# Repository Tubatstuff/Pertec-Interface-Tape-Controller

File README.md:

This is the repository for a controller to formatted Pertec tape interface.

The directories are as follows:

	doc - Documentation
	firmware - Controller firmware
	kicad - KiCAD schematics, board layout, etc.

The firmware can be built from source using the gcc-arm-none-eabi compiler
and the libopencm3 development library (libopencm3.org) which is covered by
the GNU General Public License v3.0, as is this project.

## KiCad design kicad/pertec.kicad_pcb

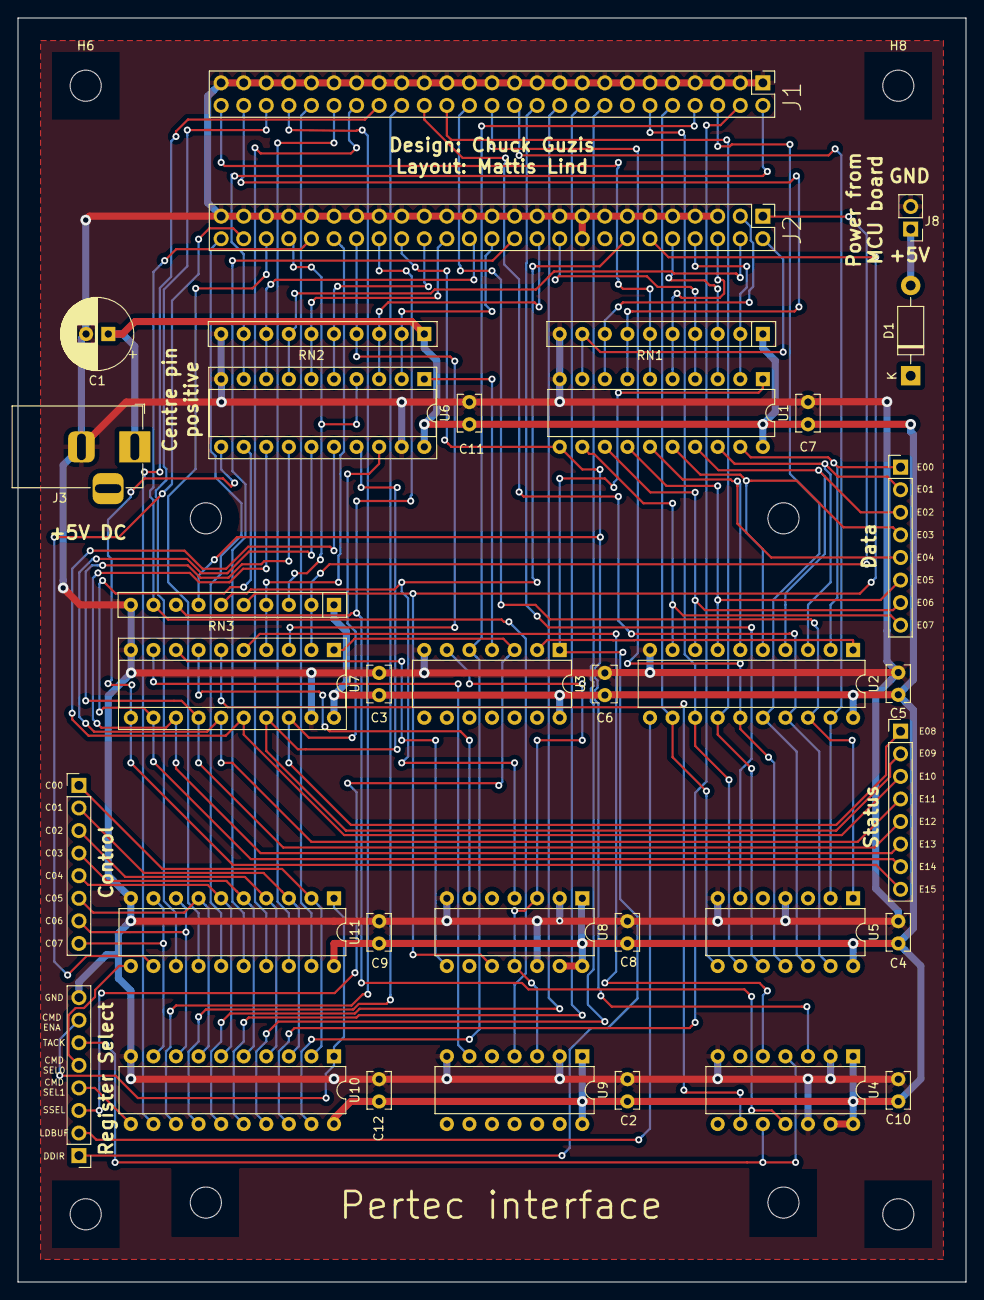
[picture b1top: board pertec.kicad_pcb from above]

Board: 2 copper layers, 106.7 x 142.2 mm, 43 parts (0 on the bottom side), 91 nets.

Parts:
C1: 470/16; CP_Radial_D8.0mm_P2.50mm
C2, C3, C4, C5, C6, C7, C8, C9, C10, C11, C12: 104; C_Rect_L4.0mm_W2.5mm_P2.50mm
D1: 1N5817; D_DO-41_SOD81_P10.16mm_Horizontal
H1, H2, H3, H4, H5, H6, H7, H8: MountingHole; MountingHole_3.5mm
J1, J2: Conn_02x25_Odd_Even; PinHeader_2x25_P2.54mm_Vertical
J3: +5 VDC; BarrelJack_Horizontal
J4: Data 0:7; PinHeader_1x08_P2.54mm_Vertical
J5: Status 0:7; PinHeader_1x08_P2.54mm_Vertical
J6: Control; PinHeader_1x08_P2.54mm_Vertical
J7: Register Select; PinHeader_1x08_P2.54mm_Vertical
J8: MCU Power; PinHeader_1x02_P2.54mm_Vertical
RN1, RN2, RN3: 220/330; R_Array_SIP10
U1, U2, U10, U11: 74LS574; DIP-20_W7.62mm
U3: 74LS04; DIP-14_W7.62mm
U4, U8, U9: 74LS74; DIP-14_W7.62mm
U5: 74LS280; DIP-14_W7.62mm
U6, U7: 74LS541; DIP-20_W7.62mm_Socket

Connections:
C00: J6.1, U10.2, U11.2
C01: J6.2, U10.3, U11.3
C02: J6.3, U10.4, U11.4
C03: J6.4, U10.5, U11.5
C04: J6.5, U10.6, U11.6
C05: J6.6, U10.7, U11.7
C06: J6.7, U10.8, U11.8
C07: J6.8, U10.9, U11.9
CMDENA: J7.7, U10.1, U11.1
CMDSEL0: J7.4, U10.11
CMDSEL1: J7.5, U11.11
DDIR: J7.1, U1.1, U3.1
E00: J4.1, U1.19, U2.2
E01: J4.2, U1.18, U2.3
E02: J4.3, U1.17, U2.4
E03: J4.4, U1.16, U2.5
E04: J4.5, U1.15, U2.6
E05: J4.6, U1.14, U2.7
E06: J4.7, U1.13, U2.8
E07: J4.8, U1.12, U2.9
E08: J5.1, U6.18, U7.18
E09: J5.2, U6.17, U7.17
E10: J5.3, U6.16, U7.16
E11: J5.4, U6.15, U7.15
E12: J5.5, U6.14, U7.14
E13: J5.6, U6.13, U7.13
E14: J5.7, U6.12, U7.12
E15: J5.8, U6.11, U7.11
GND: C1.2, C2.2, C3.2, C4.2, C5.2, C6.2, C7.2, C8.2, C9.2, C10.2, C11.2, C12.2, J1.1, J1.3, J1.5, J1.7, J1.9, J1.11, J1.13, J1.15, J1.17, J1.19, J1.21, J1.23, J1.25, J1.27, J1.29, J1.31, J1.33, J1.35, J1.37, J1.39, J1.41, J1.43, J1.45, J1.47, J1.49, J2.5, J2.7, J2.9, J2.11, J2.13, J2.15, J2.17, J2.18, J2.19, J2.21, J2.23, J2.25, J2.27, J2.29, J2.31, J2.33, J2.35, J2.37, J2.39, J2.41, J2.43, J2.45, J2.47, J2.49, J3.2, J7.8, J8.2, RN1.10, RN2.10, RN3.10, U1.10, U2.10, U3.7, U4.2, U4.7, U4.12, U5.4, U5.7, U6.10, U6.19, U7.10, U7.19, U8.2, U8.7, U8.12, U9.2, U9.7, U10.10, U11.10
ICER: J2.42, RN3.9, U9.4
IDBY: J2.38, RN2.4, U7.3
IEDIT: J1.38, U11.17
IEOT: J2.22, RN2.3, U6.3
IERASE: J1.40, U11.18
IFAD: J2.48, U11.12
IFBY: J1.2, RN2.9, U6.9
IFMK: J2.14, RN3.6, U8.4
IFPT: J2.32, RN2.5, U6.5
IGO: J1.8, U3.5, U10.19
IHER: J2.12, RN3.5, U8.10
IHSP: J2.50, U11.15
ILDP: J2.4, RN2.7, U6.7
ILOL: J1.16, U10.17
ILWD: J1.4, U10.18
IONL: J2.44, RN3.3, U6.4
IR0: J2.2, RN1.9, U1.9
IR1: J2.3, RN1.8, U1.8
IR2: J1.48, RN1.7, U1.7
IR3: J1.50, RN1.6, U1.6
IR4: J2.6, RN1.5, U1.5
IR5: J2.20, RN1.4, U1.4
IR6: J2.10, RN1.3, U1.3
IR7: J2.8, RN1.2, U1.2
IRDY: J2.28, RN2.8, U6.8
IREV: J1.18, U10.16
IREW: J1.20, U10.15
IRNZ: J2.26, RN2.2, U6.2
IRP: J2.1, RN3.2, U7.2
IRSTR: J2.34, RN3.7, U1.11, U4.3
IRTH1: J1.44, U10.13
IRTH2: J1.36, U10.12
IRWD: J2.30, RN2.6, U6.6
IRWU: J2.24, U11.16
ISPEED: J2.40, RN3.4, U7.4
ITAD0: J1.46, U11.13
ITAD1: J2.46, U11.14
IW0: J1.10, U2.12, U5.8
IW1: J1.12, U2.13, U5.9
IW2: J1.30, U2.14, U5.10
IW3: J1.26, U2.15, U5.11
IW4: J1.6, U2.16, U5.12
IW5: J1.32, U2.17, U5.13
IW6: J1.28, U2.18, U5.1
IW7: J1.24, U2.19, U5.2
IWFM: J1.42, U11.19
IWP: J1.22, U5.6
IWRT: J1.34, U10.14
IWSTR: J2.36, RN3.8, U4.11
LDBUF: J7.2, U2.11
NIGO: U3.6, U8.3, U8.11, U9.3
unnamed: D1.2, J8.1
unnamed: U2.1, U3.2
unnamed: U3.4, U6.1
unnamed: U7.7, U8.6
unnamed: U7.8, U8.8
unnamed: U7.9, U9.6
RDAVAIL: U4.5, U7.5
SSEL: J7.3, U3.3, U7.1
TACK: J7.6, U4.4, U4.10
VCC: C1.1, C2.1, C3.1, C4.1, C5.1, C6.1, C7.1, C8.1, C9.1, C10.1, C11.1, C12.1, D1.1, J3.1, RN1.1, RN2.1, RN3.1, U1.20, U2.20, U3.14, U4.1, U4.13, U4.14, U5.14, U6.20, U7.20, U8.1, U8.13, U8.14, U9.1, U9.14, U10.20, U11.20
WDEMPTY: U4.9, U7.6

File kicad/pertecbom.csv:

"Id";"Designator";"Package";"Quantity";"Designation";"Supplier and ref";
1;"C4,C8,C10,C9,C5,C12,C7,C2,C3,C6,C11";"C_Rect_L4.0mm_W2.5mm_P2.50mm";11;"104";;;
2;"J1,J2";"PinHeader_2x25_P2.54mm_Vertical";2;"Conn_02x25_Odd_Even";;;
3;"J3";"BarrelJack_Horizontal";1;"+5 VDC";;;
4;"J5";"PinHeader_1x08_P2.54mm_Vertical";1;"Status 0:7";;;
5;"J6";"PinHeader_1x08_P2.54mm_Vertical";1;"Control";;;
6;"J7";"PinHeader_1x08_P2.54mm_Vertical";1;"Register Select";;;
7;"RN2,RN1,RN3";"R_Array_SIP10";3;"220/330";;;
8;"U2,U11,U1,U10";"DIP-20_W7.62mm";4;"74LS574";;;
9;"U8,U4,U9";"DIP-14_W7.62mm";3;"74LS74";;;
10;"U7,U6";"DIP-20_W7.62mm_Socket";2;"74LS541";;;
11;"C1";"CP_Radial_D8.0mm_P2.50mm";1;"470/16";;;
12;"U3";"DIP-14_W7.62mm";1;"74LS04";;;
13;"U5";"DIP-14_W7.62mm";1;"74LS280";;;
14;"J4";"PinHeader_1x08_P2.54mm_Vertical";1;"Data 0:7";;;
15;"D1";"D_DO-41_SOD81_P10.16mm_Horizontal";1;"1N5817";;;
16;"J8";"PinHeader_1x02_P2.54mm_Vertical";1;"MCU Power";;;
